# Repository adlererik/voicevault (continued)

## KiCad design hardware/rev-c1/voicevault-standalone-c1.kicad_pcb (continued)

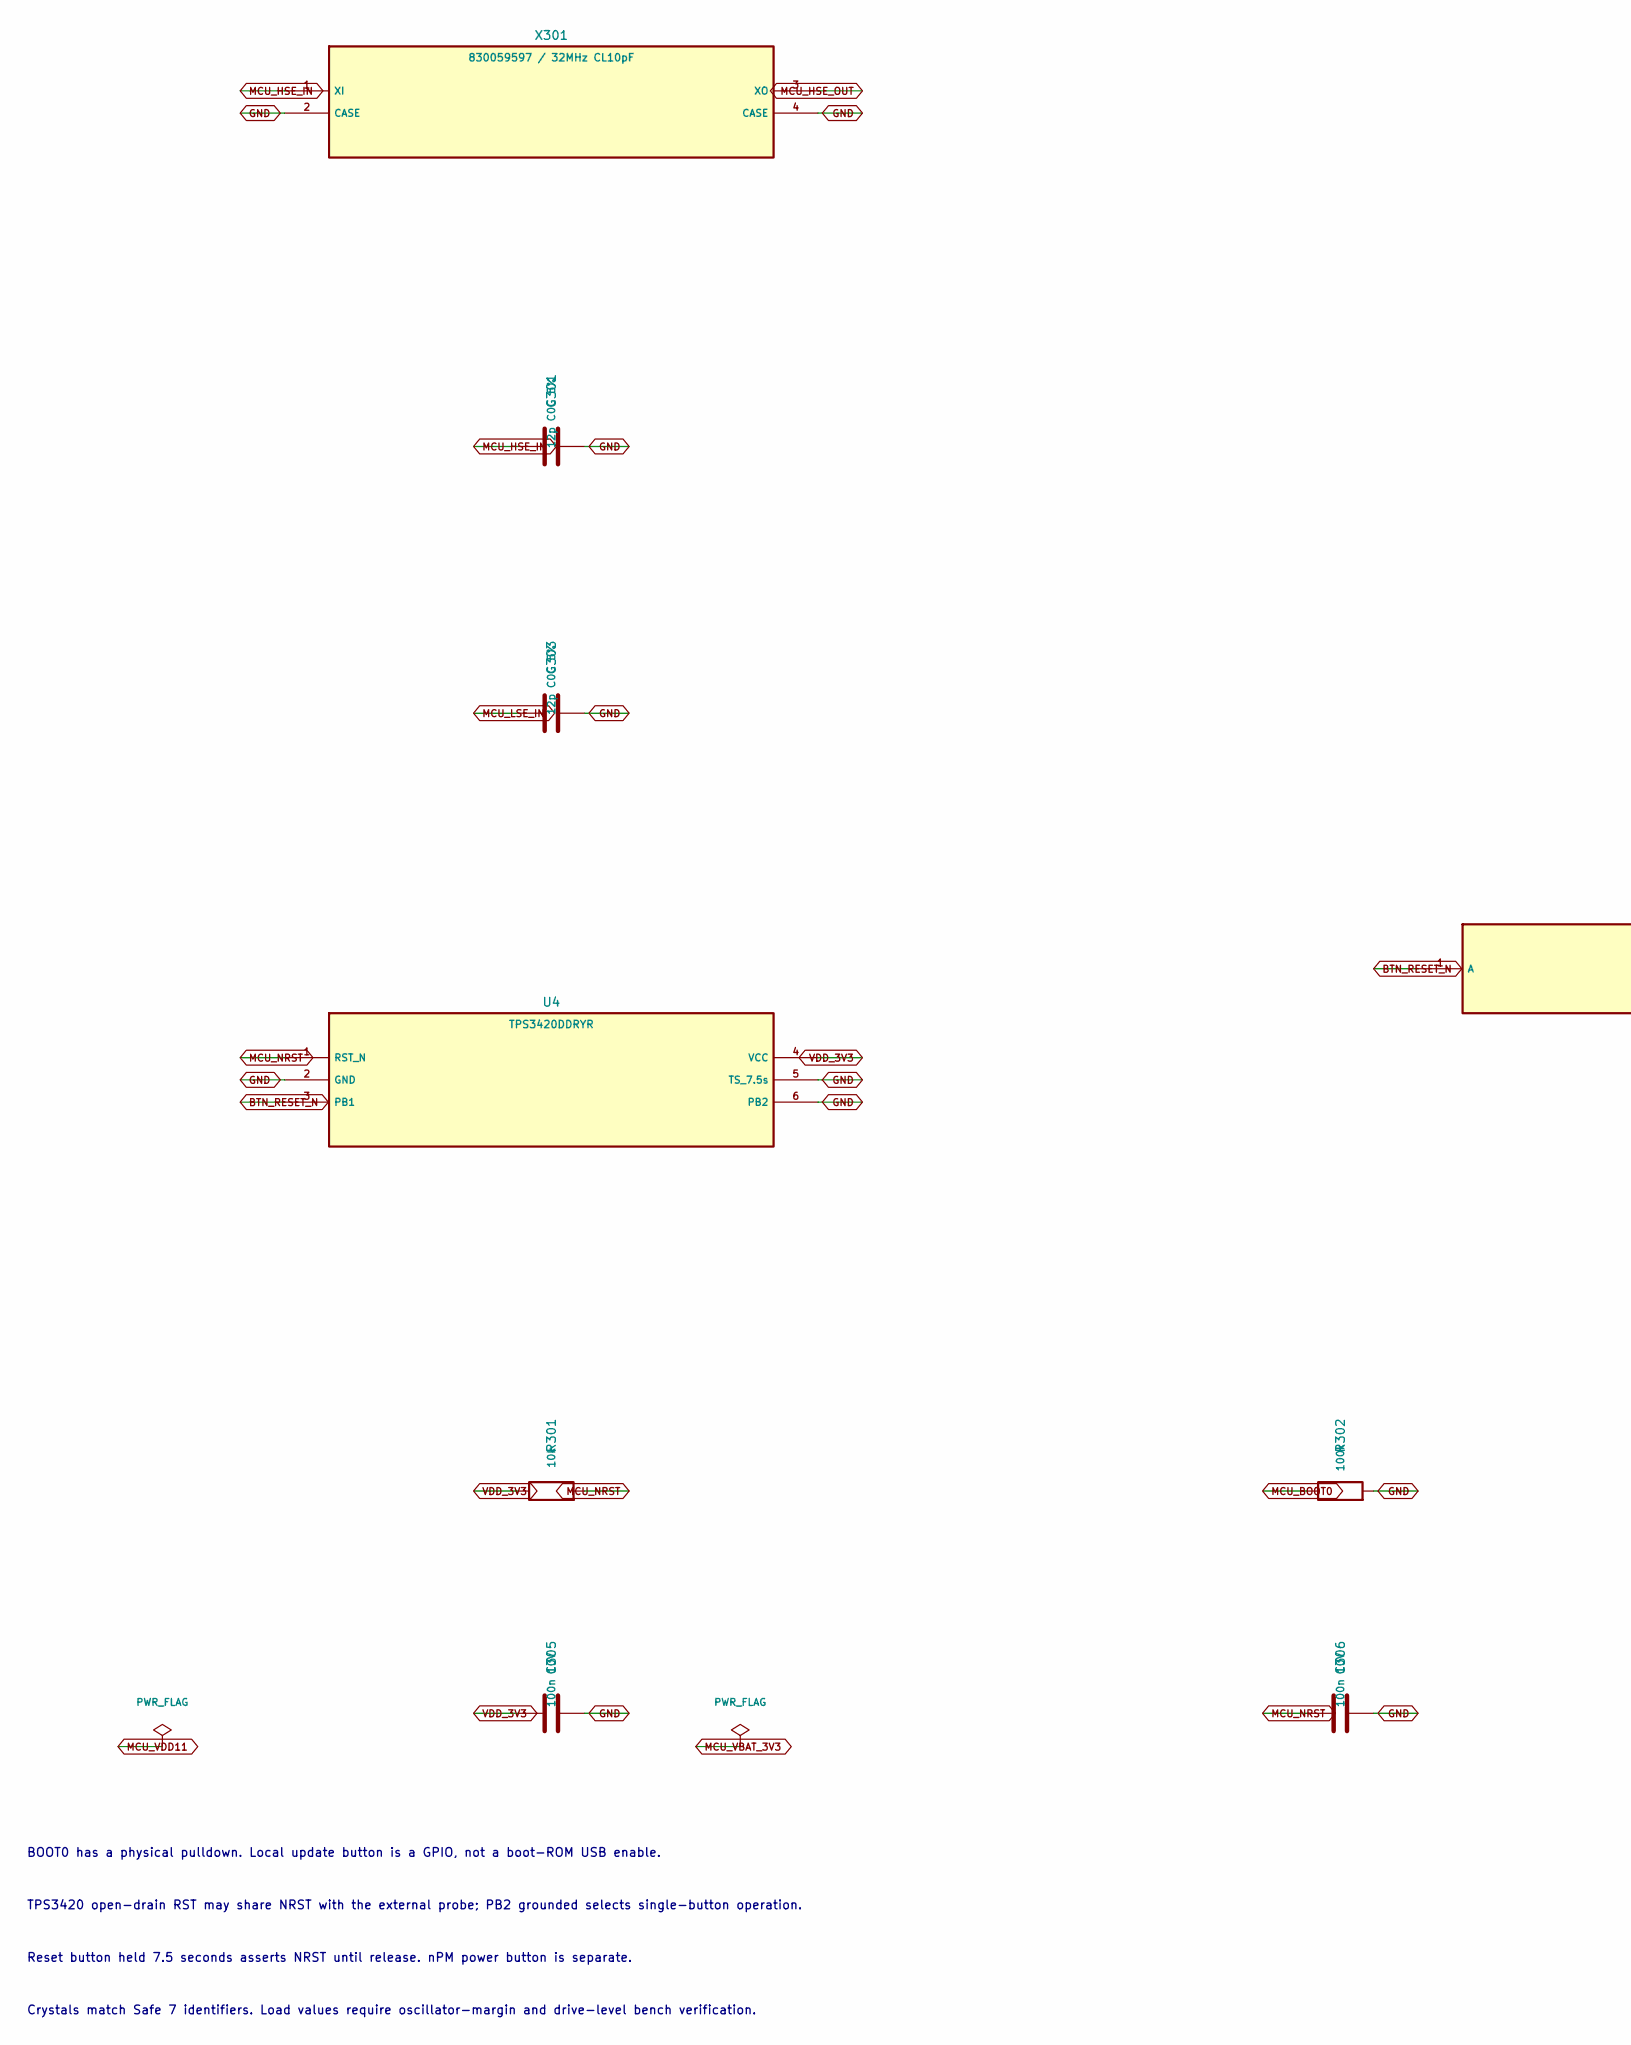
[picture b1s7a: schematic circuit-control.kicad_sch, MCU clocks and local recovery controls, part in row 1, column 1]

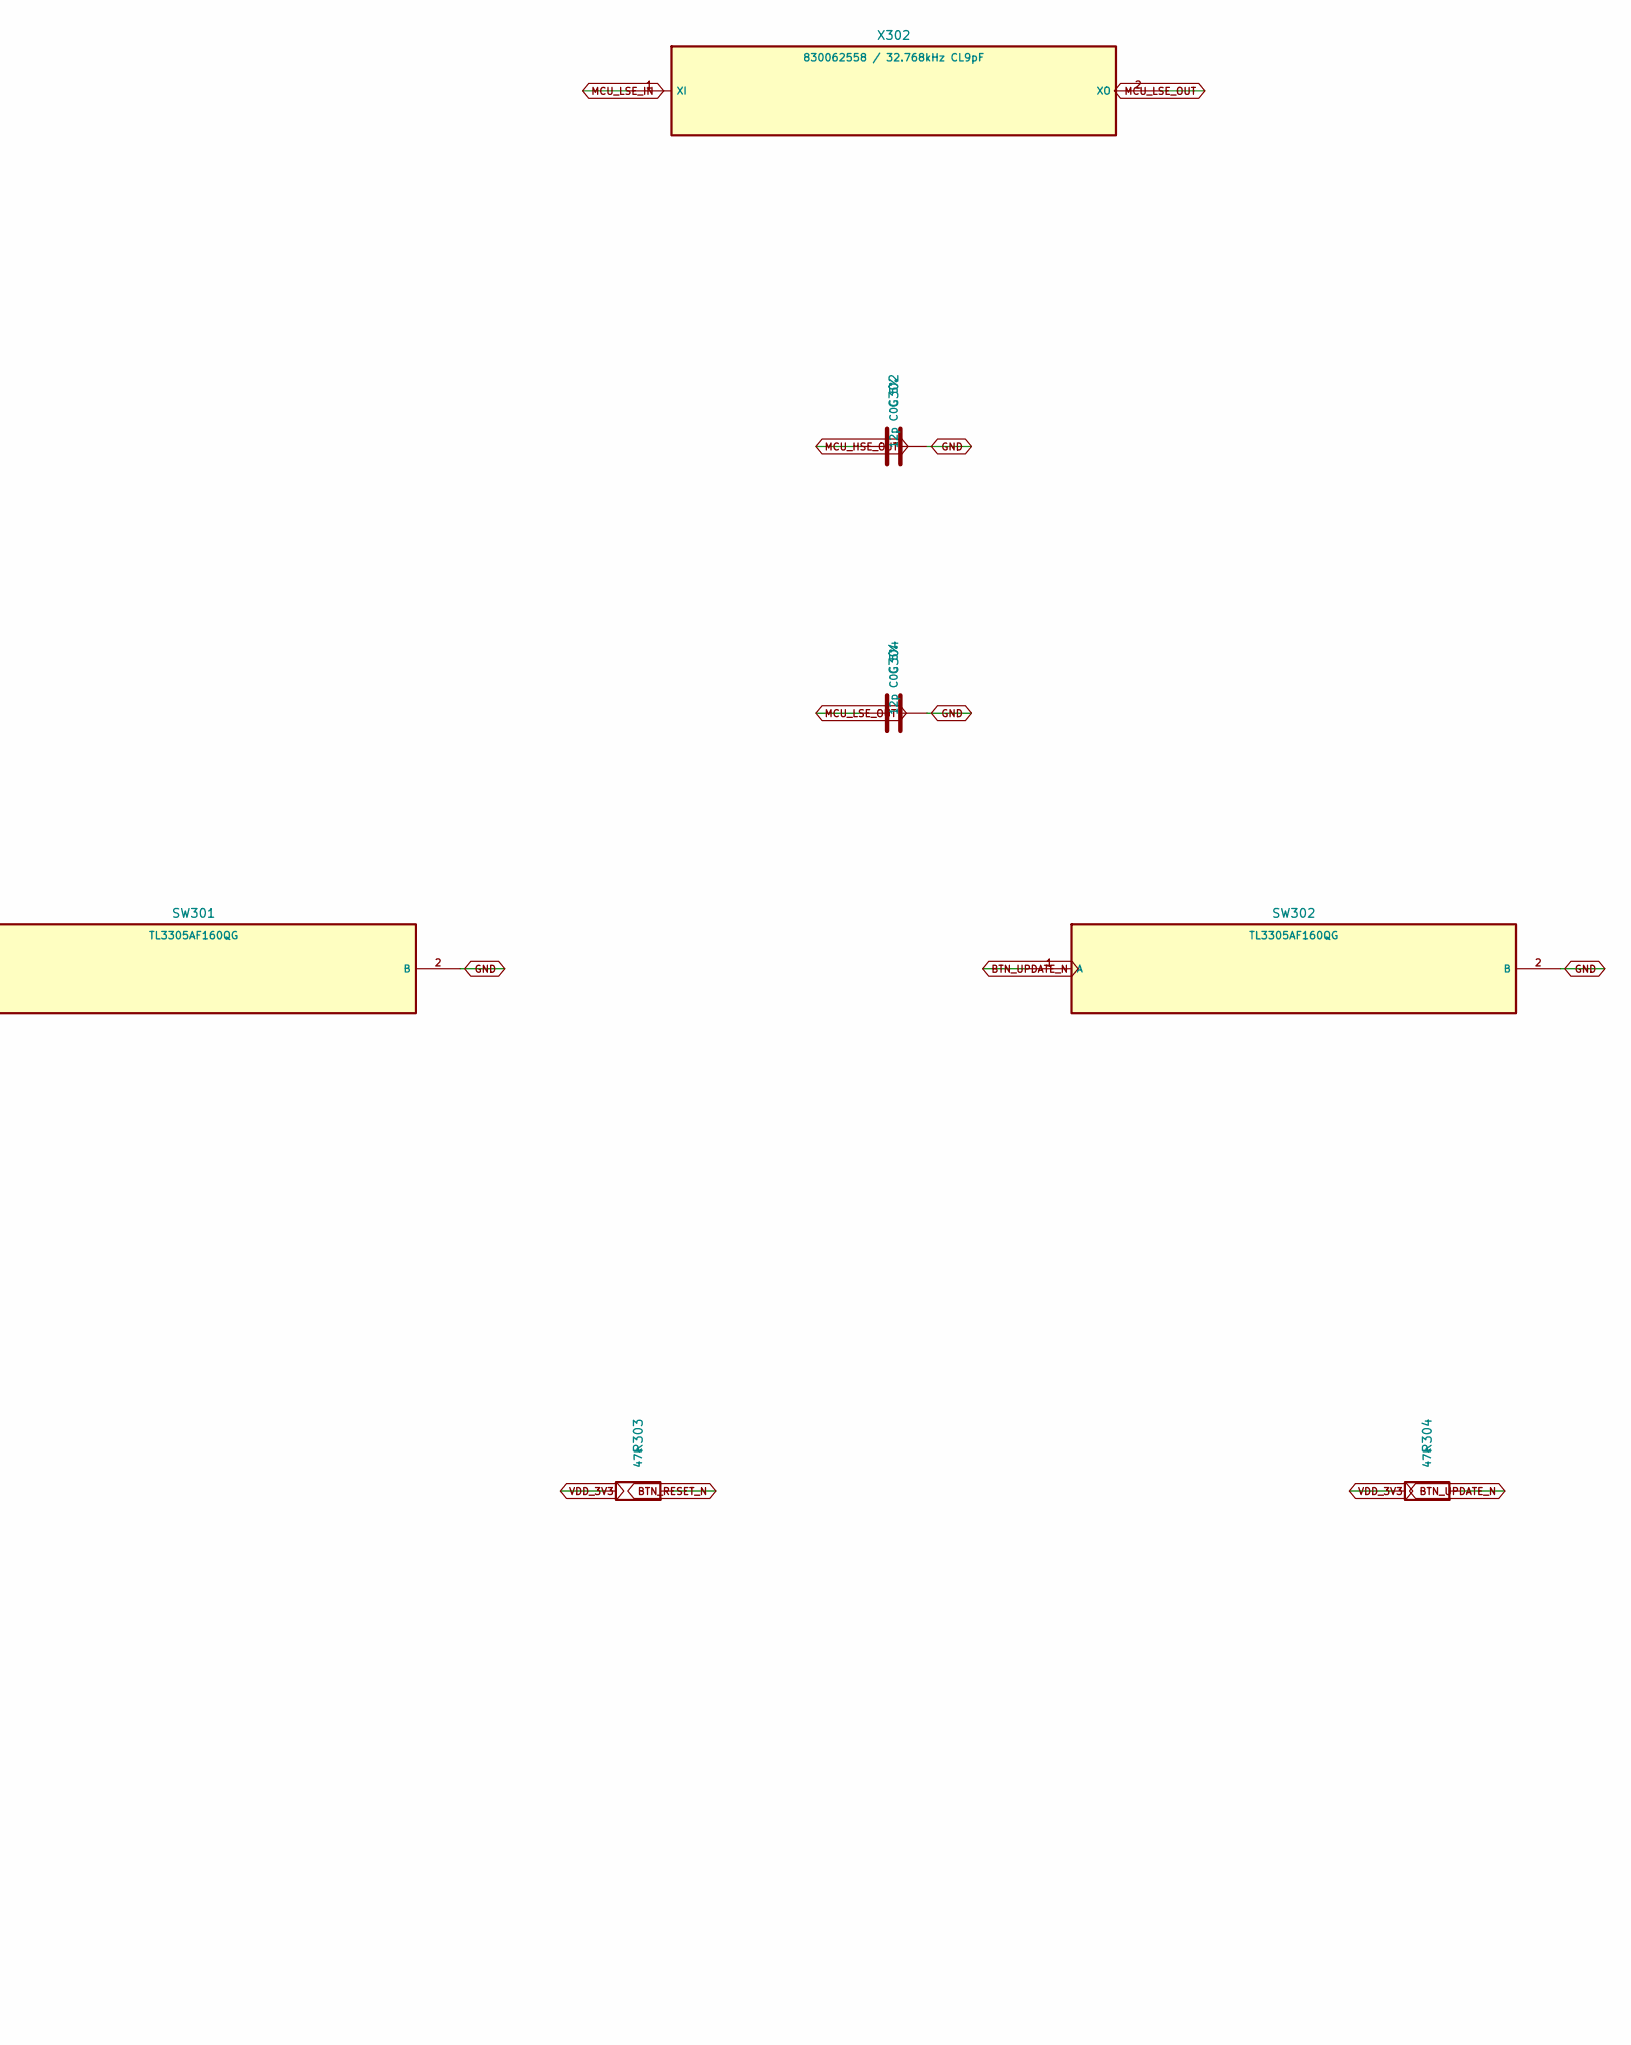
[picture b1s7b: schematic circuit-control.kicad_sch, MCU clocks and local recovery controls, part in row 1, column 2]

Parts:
C301, C302, C303, C304: 12p C0G 5%; C_0402_1005Metric
C305, C306: 100n 10V; C_0402_1005Metric
R301: 10k; R_0402_1005Metric
R302: 100k; R_0402_1005Metric
R303, R304: 47k; R_0402_1005Metric
SW301, SW302: TL3305AF160QG; SW_SPST_TL3305A
U4: TPS3420DDRYR; Texas_USON-6_1x1.45mm_P0.5mm_SMD
X301: 830059597 / 32MHz CL10pF; Crystal_SMD_2016-4Pin_2.0x1.6mm
X302: 830062558 / 32.768kHz CL9pF; Crystal_SMD_2012-2Pin_2.0x1.2mm

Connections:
BTN_RESET_N: R303.2, SW301.1 (A), U4.3 (PB1); also elsewhere on the board
BTN_UPDATE_N: R304.2, SW302.1 (A); also elsewhere on the board
GND: C301.2, C302.2, C303.2, C304.2, C305.2, C306.2, R302.2, SW301.2 (B), SW302.2 (B), U4.2 (GND), U4.5 (TS_7.5s), U4.6 (PB2), X301.2 (CASE), X301.4 (CASE); also elsewhere on the board
MCU_BOOT0: R302.1; also elsewhere on the board
MCU_HSE_IN: C301.1, X301.1 (XI); also elsewhere on the board
MCU_HSE_OUT: C302.1, X301.3 (XO); also elsewhere on the board
MCU_LSE_IN: C303.1, X302.1 (XI); also elsewhere on the board
MCU_LSE_OUT: C304.1, X302.2 (XO); also elsewhere on the board
MCU_NRST: C306.1, R301.2, U4.1 (RST_N); also elsewhere on the board
VDD_3V3: C305.1, R301.1, R303.1, R304.1, U4.4 (VCC); also elsewhere on the board

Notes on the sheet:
BOOT0 has a physical pulldown. Local update button is a GPIO, not a boot-ROM USB enable.
TPS3420 open-drain RST may share NRST with the external probe; PB2 grounded selects single-button operation.
Reset button held 7.5 seconds asserts NRST until release. nPM power button is separate.
Crystals match Safe 7 identifiers. Load values require oscillator-margin and drive-level bench verification.

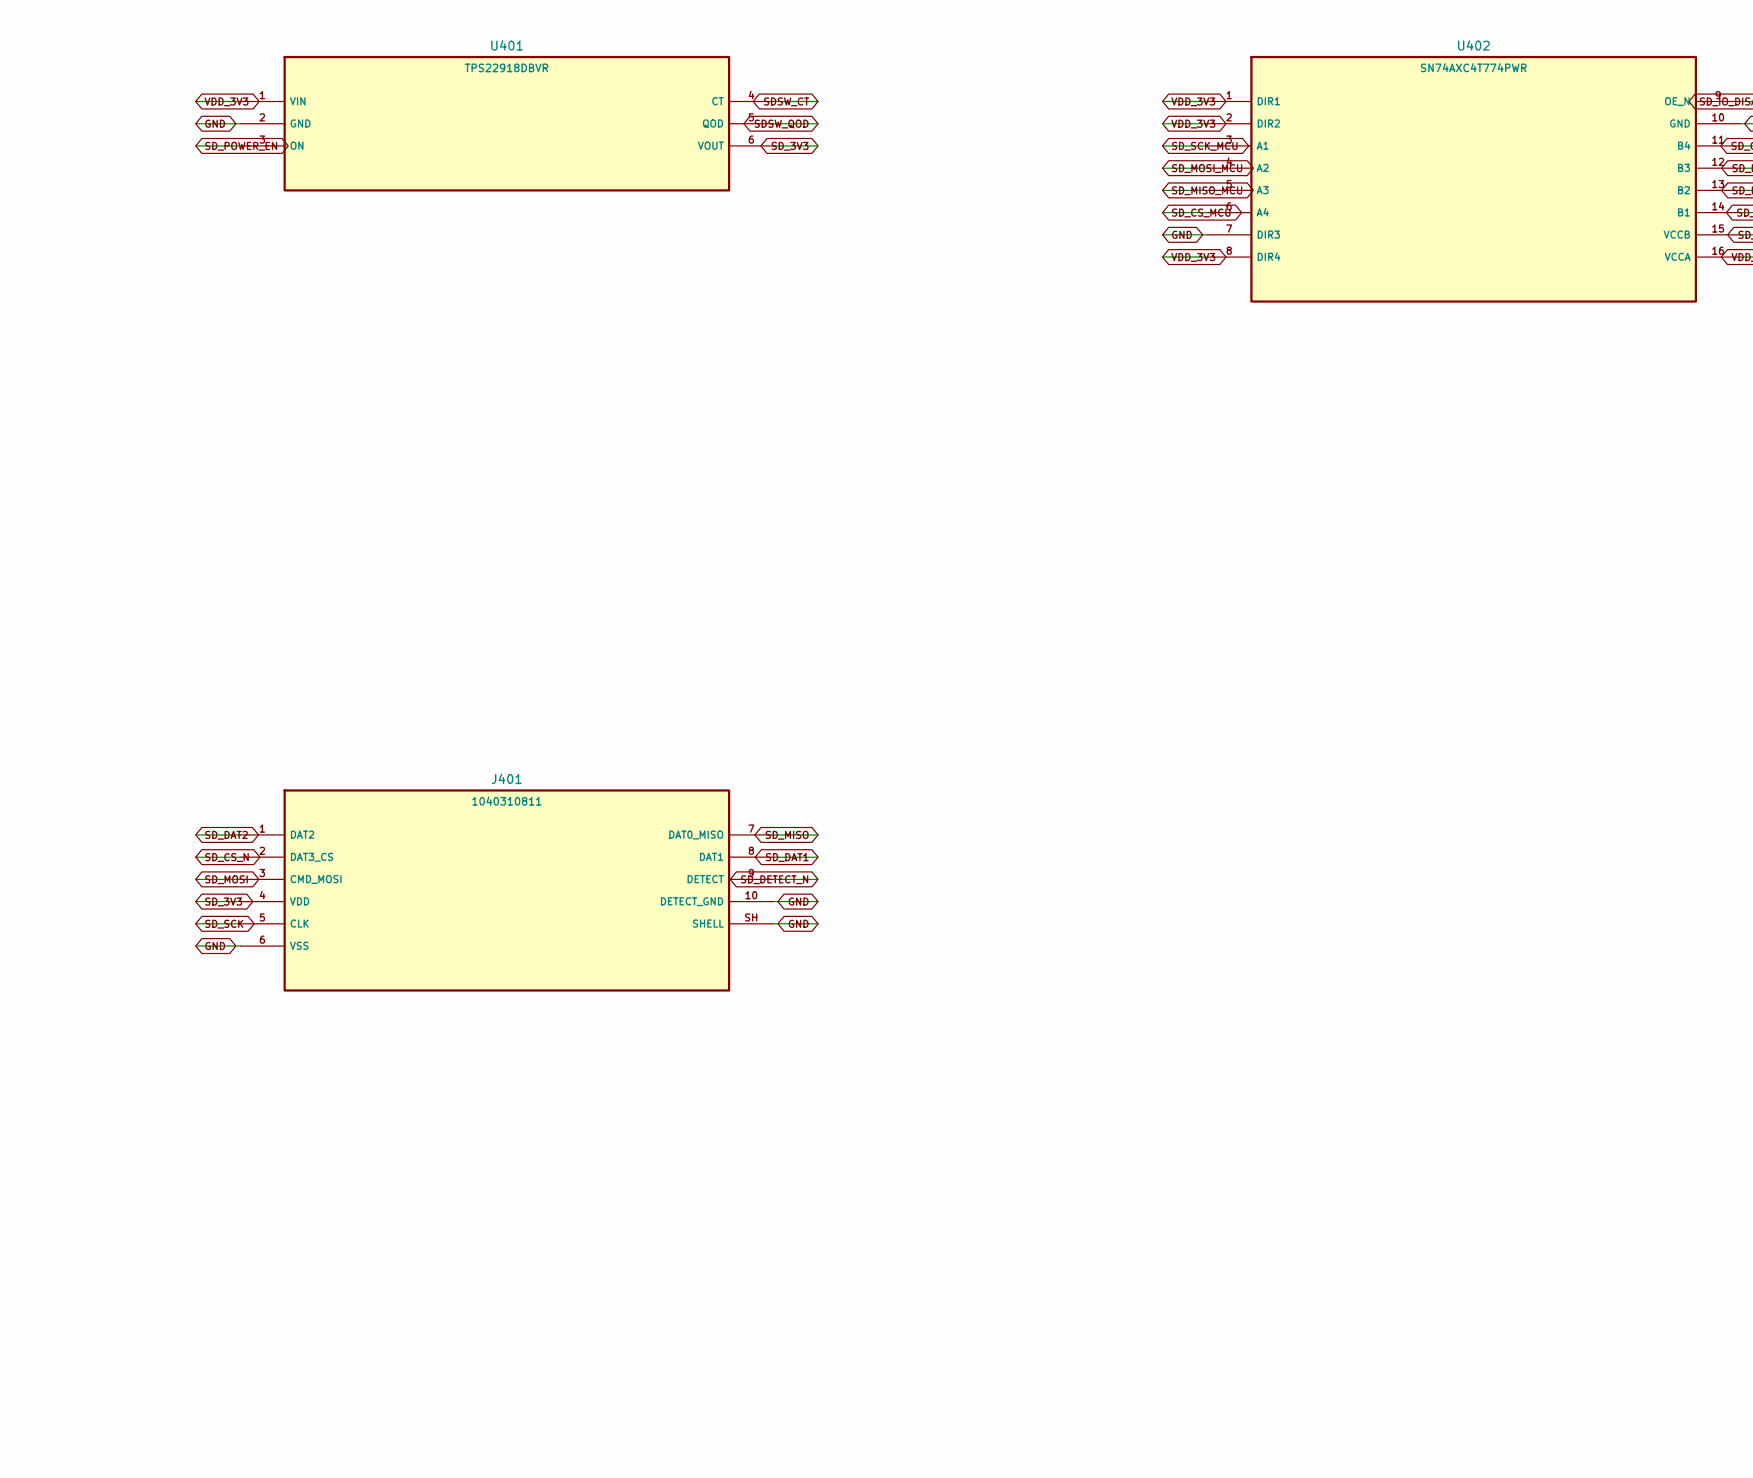
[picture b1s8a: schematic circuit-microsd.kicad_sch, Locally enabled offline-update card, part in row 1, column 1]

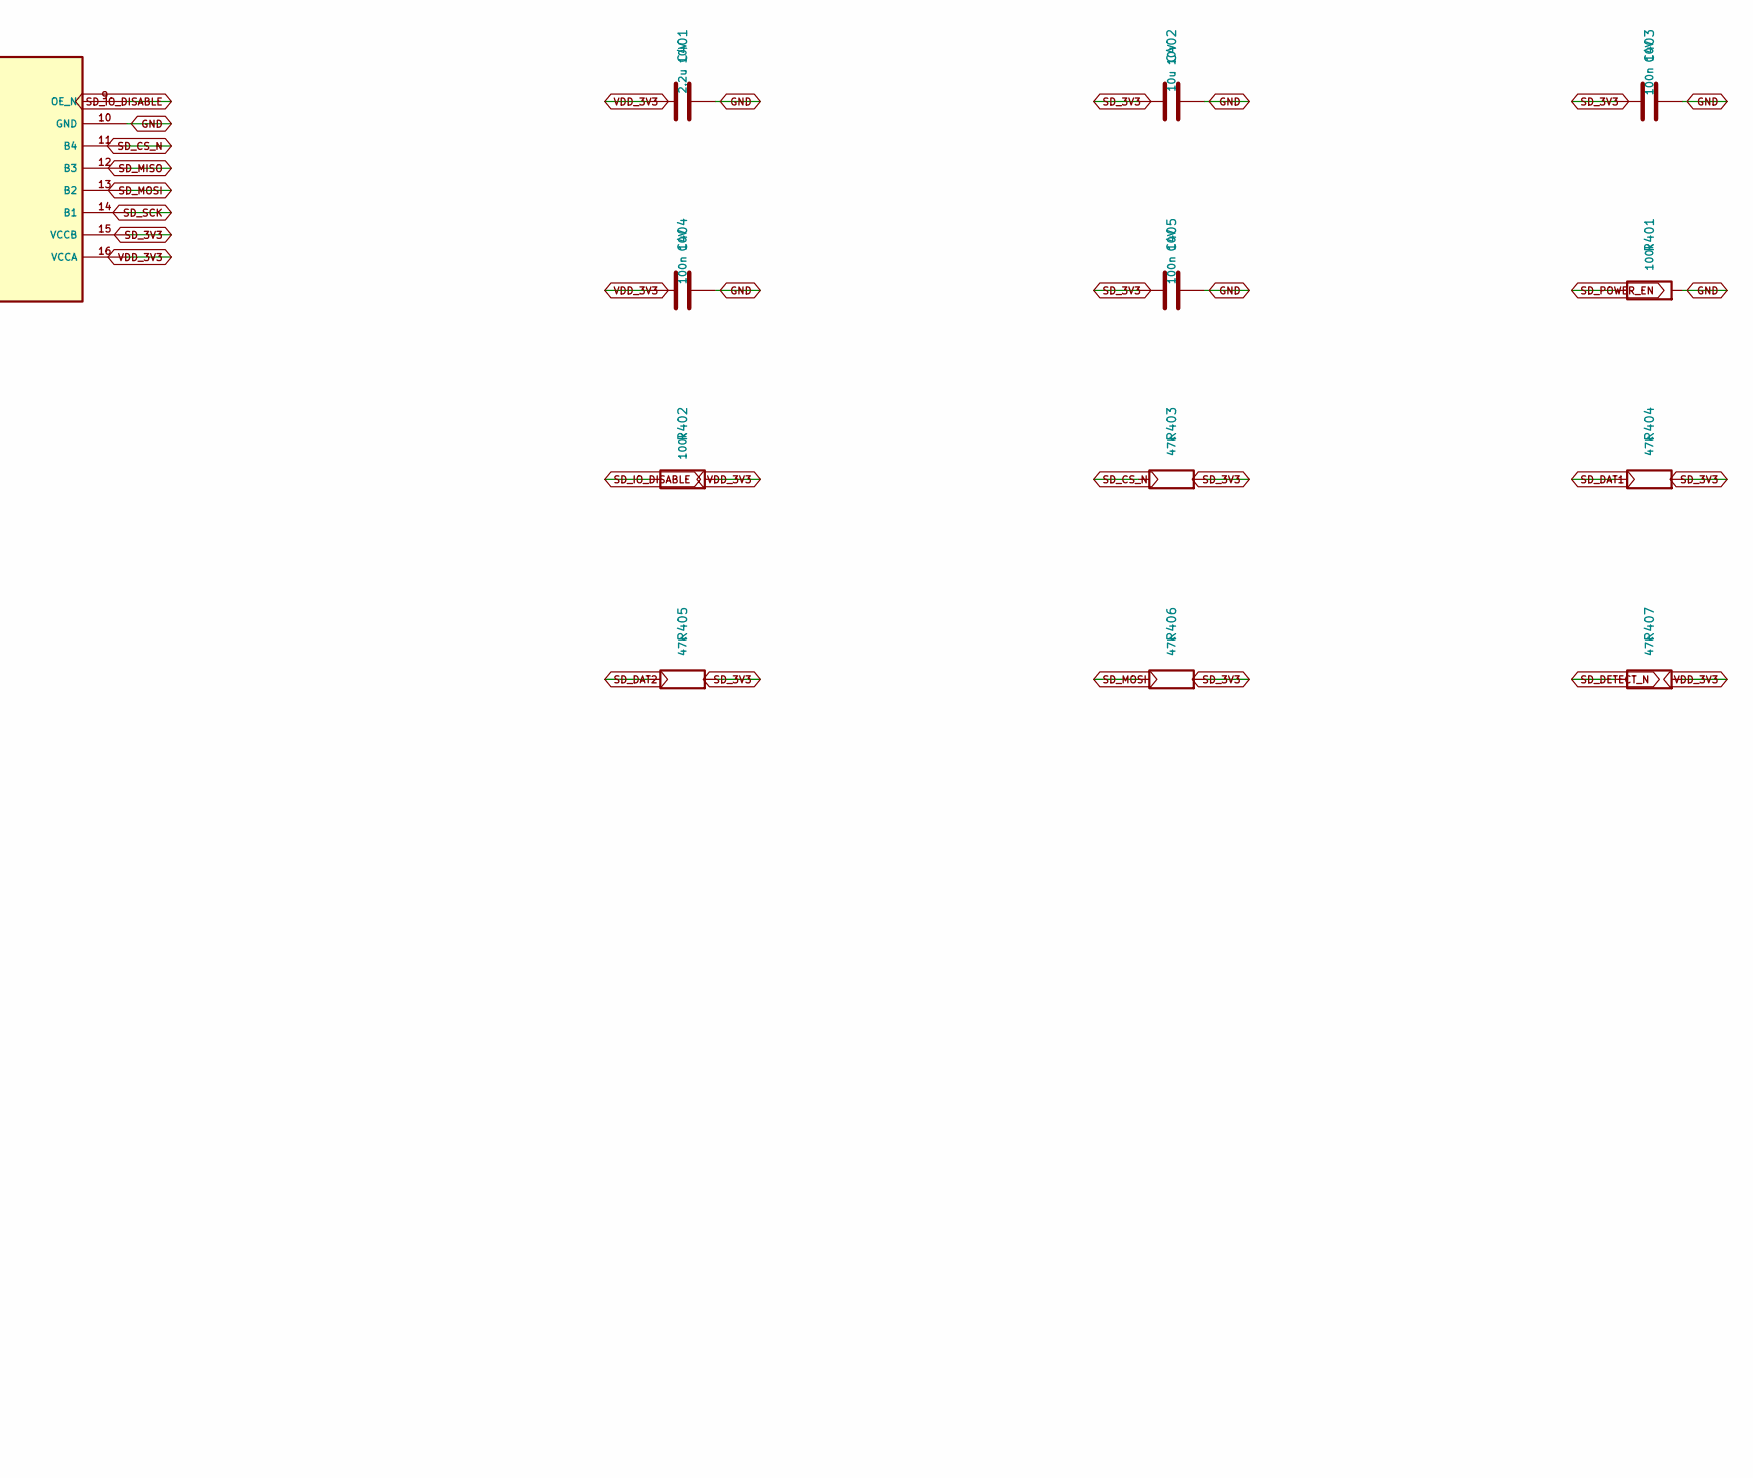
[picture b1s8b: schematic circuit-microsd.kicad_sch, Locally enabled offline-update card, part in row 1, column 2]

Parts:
C401: 2.2u 10V; C_0603_1608Metric
C402: 10u 10V; C_0805_2012Metric
C403, C404, C405: 100n 10V; C_0402_1005Metric
J401: 1040310811; microSD_HC_Molex_104031-0811
R401, R402: 100k; R_0402_1005Metric
R403, R404, R405, R406, R407: 47k; R_0402_1005Metric
U401: TPS22918DBVR; SOT-23-6
U402: SN74AXC4T774PWR; TSSOP-16_4.4x5mm_P0.65mm

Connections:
GND: C401.2, C402.2, C403.2, C404.2, C405.2, J401.6 (VSS), J401.10 (DETECT_GND), J401.SH (SHELL), R401.2, U401.2 (GND), U402.7 (DIR3), U402.10 (GND); also elsewhere on the board
SDSW_CT: U401.4 (CT); also elsewhere on the board
SDSW_QOD: U401.5 (QOD); also elsewhere on the board
SD_3V3: C402.1, C403.1, C405.1, J401.4 (VDD), R403.2, R404.2, R405.2, R406.2, U401.6 (VOUT), U402.15 (VCCB); also elsewhere on the board
SD_CS_MCU: U402.6 (A4); also elsewhere on the board
SD_CS_N: J401.2 (DAT3_CS), R403.1, U402.11 (B4)
SD_DAT1: J401.8 (DAT1), R404.1
SD_DAT2: J401.1 (DAT2), R405.1
SD_DETECT_N: J401.9 (DETECT), R407.1; also elsewhere on the board
SD_IO_DISABLE: R402.1, U402.9 (OE_N); also elsewhere on the board
SD_MISO: J401.7 (DAT0_MISO), U402.12 (B3)
SD_MISO_MCU: U402.5 (A3); also elsewhere on the board
SD_MOSI: J401.3 (CMD_MOSI), R406.1, U402.13 (B2)
SD_MOSI_MCU: U402.4 (A2); also elsewhere on the board
SD_POWER_EN: R401.1, U401.3 (ON); also elsewhere on the board
SD_SCK: J401.5 (CLK), U402.14 (B1)
SD_SCK_MCU: U402.3 (A1); also elsewhere on the board
VDD_3V3: C401.1, C404.1, R402.2, R407.2, U401.1 (VIN), U402.1 (DIR1), U402.2 (DIR2), U402.8 (DIR4), U402.16 (VCCA); also elsewhere on the board

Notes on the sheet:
TPS22918 switches regulated main 3.3V; I/O isolation remains default disabled.
Card peak current and real inrush need bench qualification; this switch is not a current limiter.
C1: hardware SPI2 clock is PB13 (pin 70), not PC0. PC1=MOSI; PC2=MISO; PC7=software CS.

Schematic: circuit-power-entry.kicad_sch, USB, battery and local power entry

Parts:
C501: 100n 16V; C_0402_1005Metric
C502: 100n 10V; C_0402_1005Metric
D503: SMF5.0A; D_SOD-123F
F501: MF-PSMF050X-2; Fuse_0805_2012Metric
J501: USB4125-GF-A; USB_C_Receptacle_GCT_USB4125-xx-x_6P_TopMnt_Horizontal
J502: S2B-PH-SM4-TB(LF)(SN); BL-5C holder harness; exac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; JST_PH_S2B-PH-SM4-TB_1x02-1MP_P2.00mm_Horizontal
J503: BM02B-SRSS-TB(LF)(SN); EXTERNAL NTC; JST_SH_BM02B-SRSS-TB_1x02-1MP_P1.00mm_Vertical
R501, R502: 5.1k 1%; R_0402_1005Metric

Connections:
BAT_PACK: C502.1, J502.1 (PACK_PLUS); also elsewhere on the board
BAT_TS: J503.1 (NTC); also elsewhere on the board
GND: C501.2, C502.2, D503.2 (A), J501.A12 (GND), J501.B12 (GND), J501.SH (SHELL), J502.2 (PACK_MINUS), J503.2 (GND), R501.2, R502.2; also elsewhere on the board
USB_5V_FUSED: C501.1, D503.1 (K), F501.2 (OUT); also elsewhere on the board
USB_5V_RAW: F501.1 (IN), J501.A9 (VBUS), J501.B9 (VBUS)
USB_CC1: J501.A5 (CC1), R501.1
USB_CC2: J501.B5 (CC2), R502.1

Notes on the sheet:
Power-only USB-C. No D+/D- or firmware transport.
BL-5C pack and holder harness require acceptance. Third BSI terminal is not temperature sensing.
J503 requires a real pack-temperature NTC; open/short sensor must inhibit charging.

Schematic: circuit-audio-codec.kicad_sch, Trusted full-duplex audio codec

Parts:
C601, C602, C603, C605: 10u 10V; C_0805_2012Metric
C604, C606, C607, C608: 100n 10V; C_0402_1005Metric
D601: BAT54WS; DLDO to ALDO pop suppression; D_SOD-323
R601, R602: 2.2k; R_0402_1005Metric
R603: 100k; R_0402_1005Metric
U601: TLV320AIC3204IRHBR; QFN-32-1EP_5x5mm_P0.5mm_EP3.45x3.45mm

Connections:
AUD_ADC_DATA: U601.5 (DOUT); also elsewhere on the board
AUD_AVDD_1V8: C601.1, C607.1, D601.1 (K), U601.24 (AVDD_ALDO_OUT)
AUD_BCLK: U601.2 (BCLK); also elsewhere on the board
AUD_DAC_DATA: U601.4 (DIN); also elsewhere on the board
AUD_DVDD_1V72: C602.1, C608.1, D601.2 (A), U601.29 (DVDD_DLDO_OUT)
AUD_HPL_DC: U601.25 (HPL); also elsewhere on the board
AUD_HPR_DC: U601.27 (HPR); also elsewhere on the board
AUD_LDOIN_2V8: C605.1, C606.1, U601.26 (LDOIN_HPVDD); also elsewhere on the board
AUD_MCLK: U601.1 (MCLK); also elsewhere on the board
AUD_MICBIAS: U601.19 (MICBIAS); also elsewhere on the board
AUD_REF: C603.1, U601.18 (REF)
AUD_RESET_N: R603.1, U601.31 (RESET_N); also elsewhere on the board
AUD_SCL: R601.1, U601.9 (SCL); also elsewhere on the board
AUD_SDA: R602.1, U601.10 (SDA); also elsewhere on the board
AUD_WCLK: U601.3 (WCLK); also elsewhere on the board
GND: C601.2, C602.2, C603.2, C604.2, C605.2, C606.2, C607.2, C608.2, R603.2, U601.7 (IOVSS), U601.8 (SCLK_MFP3), U601.12 (SPI_SELECT_I2C), U601.17 (AVSS), U601.28 (DVSS), U601.33 (EP_GND); also elsewhere on the board
MIC_ADC: U601.13 (IN1_L); also elsewhere on the board
VDD_3V3: C604.1, R601.2, R602.2, U601.6 (IOVDD), U601.30 (LDO_SELECT_INTERNAL); also elsewhere on the board

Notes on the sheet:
TI SLOS602E pins/package; SLAA492A internal DLDO/ALDO sequence with DVDD-to-AVDD Schottky diode.
IOVDD uses VDD_3V3; LDOIN has a separate switched 500mA-capable regulator. LDO_SELECT high enables internal 1.72V DLDO; AVDD/DVDD are not tied to 3.3V.
Hold RESET low while rails settle; wait at least 1ms after reset before writes, enable ALDO at >=DLDO voltage, then ADC/DAC.
SAI1 AF13: PE2 MCLK_A, PE3 SD_B capture, PE4 FS_A, PE5 SCK_A, PE6 SD_A playback.
Audio I2C2 PF0/PF1 and SAI are connected only to the trusted MCU; no radio wires.

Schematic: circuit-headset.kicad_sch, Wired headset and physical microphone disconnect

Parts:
C609: 1u 10V X7R; C_0603_1608Metric
C610: 33p C0G; C_0402_1005Metric
C611, C612: 220u 6.3V polymer; exact MPN qualification pending; CP_EIA-7343-31_Kemet-D
D602, D603, D604: PESD5V0S1BA,115; bidirectional ESD; D_SOD-323
J601: SJ-43514-SMT-TR; CTIA headset; SJ43514SMT
R604: 2.2k 1%; R_0402_1005Metric
R605: 1k 1%; R_0402_1005Metric
R606, R607: 10R 1% 0.1W; R_0402_1005Metric
SW601: JS102011SAQN; physical microphone disconnect; SW_SPDT_CK_JS102011SAQN

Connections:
AUD_HPL_DC: C611.1 (PLUS); also elsewhere on the board
AUD_HPR_DC: C612.1 (PLUS); also elsewhere on the board
AUD_MICBIAS: R604.1; also elsewhere on the board
GND: C610.2, D602.2 (RETURN), D603.2 (RETURN), D604.2 (RETURN), J601.4 (RING2_GND), SW601.3 (MUTE_GROUND); also elsewhere on the board
HEADSET_L: D602.1 (LINE), J601.2 (TIP_LEFT), R606.2
HEADSET_MIC: D604.1 (LINE), J601.1 (SLEEVE_MIC), SW601.1 (TALK)
HEADSET_R: D603.1 (LINE), J601.3 (RING1_RIGHT), R607.2
HP_L_AC: C611.2 (MINUS), R606.1
HP_R_AC: C612.2 (MINUS), R607.1
MIC_ADC: C609.2, C610.1; also elsewhere on the board
MIC_BIASED: R604.2, R605.1, SW601.2 (COMMON)
MIC_COUPLE: C609.1, R605.2

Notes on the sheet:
CTIA only: Tip L, ring1 R, ring2 GND, sleeve MIC. OMTP requires an external passive adapter.
Mute switch disconnects headset microphone and grounds codec-side input; bias is after the disconnect.
No built-in microphone or speaker. Headphone outputs are independently AC coupled; never short HPL/HPR together.
220u coupling and 10R series values are evaluated in SPICE; exact capacitor MPN and headset/audio quality need qualification.
ESD parts are protective design elements, not a claim of tested IEC immunity.

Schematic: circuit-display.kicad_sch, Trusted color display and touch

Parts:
C701: 4.7u 10V; C_0603_1608Metric
C702: 100n 10V; C_0402_1005Metric
C703: 1u 10V; C_0603_1608Metric
J701: FH12-40S-0.5SH(55); TFT FFC; Hirose_FH12-40S-0.5SH_1x40-1MP_P0.50mm_Horizontal
J702: 2005280060; TOUCH FFC; Molex_200528-0060_1x06-1MP_P1.00mm_Horizontal
R701, R702: 4.7k; R_0402_1005Metric
R703, R704: 100k; R_0402_1005Metric
R705, R706: 47k; R_0402_1005Metric

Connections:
BL_ANODE: J701.38 (LED_A); also elsewhere on the board
BL_K1: J701.34 (LED_K1); also elsewhere on the board
BL_K2: J701.35 (LED_K2); also elsewhere on the board
BL_K3: J701.36 (LED_K3); also elsewhere on the board
BL_K4: J701.37 (LED_K4); also elsewhere on the board
GND: C701.2, C702.2, C703.2, J701.1 (GND), J701.12 (WRX_UNUSED), J701.13 (RDX_UNUSED), J701.14 (DB0), J701.15 (DB1), J701.16 (DB2), J701.17 (DB3), J701.18 (DB4), J701.19 (DB5), J701.20 (DB6), J701.21 (DB7), J701.22 (DB8), J701.23 (DB9), J701.24 (DB10), J701.25 (DB11), J701.26 (DB12), J701.27 (DB13), J701.28 (DB14), J701.29 (DB15), J701.33 (GND), J701.39 (GND), J702.2 (VSS), R703.2, R704.2; also elsewhere on the board
LCD_CS_N: J701.10 (CSX), R705.1; also elsewhere on the board
LCD_RESET_N: J701.30 (RESX), R703.1; also elsewhere on the board
LCD_SCK: J701.11 (DCX_SCL); also elsewhere on the board
LCD_SDI: J701.9 (SDA); also elsewhere on the board
LCD_SDO: J701.6 (SDO); also elsewhere on the board
LCD_TE: J701.40 (TE); also elsewhere on the board
TOUCH_IRQ_N: J702.5 (INT_N), R706.1; also elsewhere on the board
TOUCH_RESET_N: J702.6 (RESET_N), R704.1; also elsewhere on the board
TOUCH_SCL: J702.3 (SCL), R701.1; also elsewhere on the board
TOUCH_SDA: J702.4 (SDA), R702.1; also elsewhere on the board
VDD_3V3: C701.1, C702.1, C703.1, J701.7 (VDD), J701.8 (VDDI), J701.31 (IM0_SPI), J701.32 (IM2_SPI), J702.1 (VDD), R701.2, R702.2, R705.2, R706.2; also elsewhere on the board

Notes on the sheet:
Newhaven NHD-2.4-240320AF-CTXP-CTP: 3-wire, 9-bit SPI3; IM0/IM2 high. Unused WR/RD/DB grounded per module wiring diagram.
IOVDD/LCD/touch use trusted MCU rail; hold both resets low until firmware confirms 3.3V.
Touch uses I2C5 PD0/PD1 AF4, separate from power, audio and secure-element buses.
Connector equivalents are bottom-contact 40x0.5mm and 6x1.0mm. Verify actual flex thickness, pin-1 and bend clearance.
Display is a separately procured assembly, not an IC mounted by the board assembler.

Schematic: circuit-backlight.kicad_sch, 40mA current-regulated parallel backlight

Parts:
C704: 2.2u 10V; C_0603_1608Metric
C705: 1u 50V X7R; C_0805_2012Metric
D701: BZT52H-C6V2,115; open-load clamp; D_SOD-123F
L701: SRN4018-220M / 22uH; L_Bourns-SRN4018
R707: 12R 1% 0.1W; R_0402_1005Metric
R708: 100k; R_0402_1005Metric
R709, R710, R711, R712: 200R 1% 0.25W; R_0805_2012Metric
U9: TPS61062YZFR; TPS61062_YZF8_REVIEW

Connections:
BACKLIGHT_PWM: R708.1, U9.A2 (EN); also elsewhere on the board
BL_ANODE: C705.1, D701.1 (K), U9.C1 (OUT); also elsewhere on the board
BL_FB: D701.2 (A), R707.1, R709.2, R710.2, R711.2, R712.2, U9.B3 (FB)
BL_K1: R709.1; also elsewhere on the board
BL_K2: R710.1; also elsewhere on the board
BL_K3: R711.1; also elsewhere on the board
BL_K4: R712.1; also elsewhere on the board
BL_SW: L701.2, U9.C2 (SW)
GND: C704.2, C705.2, R707.2, R708.2, U9.A1 (GND), U9.A3 (ILED_500mV), U9.C3 (PGND); also elsewhere on the board
VSYS: C704.1, L701.1, U9.B1 (VIN); also elsewhere on the board

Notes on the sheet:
TPS61062 constant-current mode: ILED grounded, 0.5V / 12R = 41.7mA nominal total; tolerance minimum 40.0mA.
Four 200R / 0.25W ballast resistors share branch current; include zener-clamp and open-LED fault sensitivity.
Boost input is VSYS directly; its worst-case current exceeds the PMIC load-switch 100mA rating. AUX buck budget remains a gate.
PWM at <=1kHz, default-low EN. Initial total backlight current is approximately 42mA.
6.2V zener provides alternate feedback path on open load; output capacitor is rated 50V for device OVP.
YZF land-pattern geometry still needs exact manufacturer package-drawing review; do not release fabrication.
Input is raw VSYS (2.7-6V driver range), with full operation gated at VSYS >=3.6V pending bench qualification; do not use the MCU/AUX buck for boost input.

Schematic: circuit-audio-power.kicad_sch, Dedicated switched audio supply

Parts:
C614, C615: 2.2u 10V; C_0603_1608Metric
R608: 100k; R_0402_1005Metric
R609: 0R - removable audio-current link; R_0603_1608Metric
U602: TPS7A2028PDBVR; SOT-23-5

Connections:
AUD_2V8_REG: C615.1, R609.1, U602.5 (OUT)
AUD_LDOIN_2V8: R609.2; also elsewhere on the board
AUD_POWER_EN: R608.1, U602.3 (EN); also elsewhere on the board
GND: C614.2, C615.2, R608.2, U602.2 (GND); also elsewhere on the board
VDD_3V3: C614.1, U602.1 (IN); also elsewhere on the board

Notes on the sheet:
Dedicated 2.8V low-noise audio LDO from regulated main supply, default off.
Codec LDOIN range 1.9-3.6V. Revalidate headphone settings/sequence for 2.8V; no acoustic claim.

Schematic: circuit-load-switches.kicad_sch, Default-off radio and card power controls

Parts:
C1207: 100n 10V; C_0603_1608Metric
C1208: 10n; C_0603_1608Metric
R1205: 232k 1%; R_0402_1005Metric
R1206: 100; R_0402_1005Metric
R1207: 100k; R_0402_1005Metric
R1210: 47k; R_0402_1005Metric
R1211: 3.3k; R_0402_1005Metric
U1202: TPS2553DBVR; SOT-23-6

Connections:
GND: C1207.2, C1208.2, R1205.2, R1207.2, R1211.2, U1202.2 (GND); also elsewhere on the board
RADIO_3V3: R1211.1, U1202.6 (OUT); also elsewhere on the board
RADIO_FAULT_N: R1210.1, U1202.4 (FAULT_N); also elsewhere on the board
RADIO_POWER_EN: R1207.1, U1202.3 (EN); also elsewhere on the board
RADSW_ILIM: R1205.1, U1202.5 (ILIM)
SDSW_CT: C1208.1; also elsewhere on the board
SDSW_QOD: R1206.1; also elsewhere on the board
SD_3V3: R1206.2; also elsewhere on the board
VDD_3V3: C1207.1, R1210.2, U1202.1 (IN); also elsewhere on the board

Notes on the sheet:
Radio: TPS2553 current-limited/reverse-blocking switch, 232k ILIM, default disabled, local fault input.
Card: TPS22918 controlled slew/discharge; not overcurrent/reverse-current isolation.
Radio and card interface isolation remains required while their supplies are off.

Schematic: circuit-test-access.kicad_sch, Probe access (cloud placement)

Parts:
TP1: PROBE VSYS; TestPoint_Pad_D1.0mm
TP2, TP14: PROBE GND; TestPoint_Pad_D1.0mm
TP3: PROBE VDD_3V3; TestPoint_Pad_D1.0mm
TP4: PROBE REG_ENABLE; TestPoint_Pad_D1.0mm
TP5: PROBE MCU_VDD11; TestPoint_Pad_D1.0mm
TP6: PROBE RADIO_3V3; TestPoint_Pad_D1.0mm
TP7: PROBE SE_VCC; TestPoint_Pad_D1.0mm
TP8: PROBE SE_SCL; TestPoint_Pad_D1.0mm
TP9: PROBE SD_3V3; TestPoint_Pad_D1.0mm
TP10: PROBE SE_SDA; TestPoint_Pad_D1.0mm
TP11: PROBE AUD_LDOIN_2V8; TestPoint_Pad_D1.0mm
TP13: PROBE BAT_PACK; TestPoint_Pad_D1.0mm

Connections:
AUD_LDOIN_2V8: TP11.1; also elsewhere on the board
BAT_PACK: TP13.1; also elsewhere on the board
GND: TP2.1, TP14.1; also elsewhere on the board
MCU_VDD11: TP5.1; also elsewhere on the board
RADIO_3V3: TP6.1; also elsewhere on the board
REG_ENABLE: TP4.1; also elsewhere on the board
SD_3V3: TP9.1; also elsewhere on the board
SE_SCL: TP8.1; also elsewhere on the board
SE_SDA: TP10.1; also elsewhere on the board
SE_VCC: TP7.1; also elsewhere on the board
VDD_3V3: TP3.1; also elsewhere on the board
VSYS: TP1.1; also elsewhere on the board
